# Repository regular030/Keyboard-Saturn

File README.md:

# **Keyboard Saturn, A Simple Keyboard With An OLED Display**

# **YouTube Video:**
https://youtu.be/Gn7tNZ5N1NY

# **Why Did I Make This**

After Hackpad, I started getting recommended lots of Scotto Keebs videos on YouTube, which made me much more interested in making my own keyboard. Now that I have more free time, I decided to make my 5-month-in-thought project a reality.

# **Design Choices**
- SN74HC165N
  - Instead of using any other GPIO expanders, I wanted to use the SN because it is an 8-bit parallel-load shift register, instead of using the I2C protocol to communicate with the MCU, which is around 8 times faster
- Raspberry Pi Pico
  - Cheap and Reliable
- OLED 32-128
  -  Just wanted to add a display where I can show whether or not NUM/CAPS/SCRL lock is on, + show Spotify music, + other stuff
- 100% Layout
  - I use the Numpad for anything numbers-related
- Minimalist chassis design
  - I just wanted to make something  that was simple and looked clean, kind of like Cybertruck, but better 
 
# **Files**
<br>
chassis
<br>

- .Step files for the chassis + PCB
  - KeyboardL.step
      - Bottom left side of keyboard
  - KeyboardM.step
      - Bottom middle side of keyboard
  - KeyboardR.step
      - Bottom right side of keyboard
  - KeyboardTop.step
      - Top side of the keyboard
      - Use M2 screws to screw it into the bottom parts (screw holes in top and bottom in the middle, left and right sections) 
  - insert-keyboard v1.step
      - The inserts for the keyboard to connect KeyboardM, KeyboardL and KeyboardR, please use super glue to make sure they are in, then super glue the chassis together
<br>
kicad
<br>

- All the KiCad 8.0.5 files for the project 

# **BOM:**

https://docs.google.com/spreadsheets/d/1oLEcZ3zztSK3hqa6-qvamrNF2S6u_cLABAHxks2xx3M/edit?usp=sharing

# THIS PROJECT IS NOW DEPRECATED. IT WILL NOT BE GETTING ANY MORE SUPPORT. V2 is a possibility

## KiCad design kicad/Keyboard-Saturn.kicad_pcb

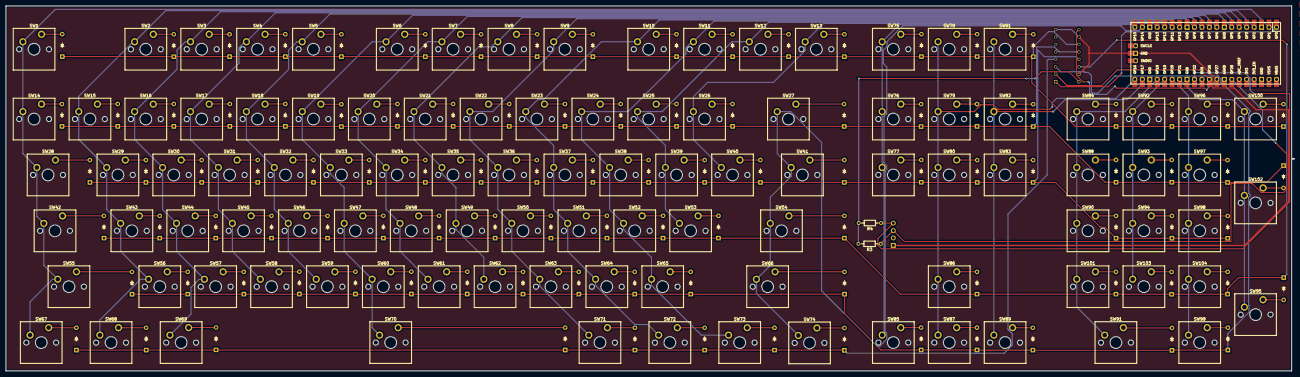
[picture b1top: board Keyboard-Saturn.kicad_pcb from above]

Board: 2 copper layers, 438.9 x 124.3 mm, 213 parts (1 on the bottom side), 138 nets.

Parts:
D1, D2, D3, D4, D5, D6, D7, D8, D9, D10, D11, D12, D13, D14, D15, D16, D17, D18, D19, D20, D21, D22, D23, D24, D25, D26, D27, D28, D29, D30, D31, D32, D33, D34, D35, D36, D37, D38, D39, D40, D41, D42, D43, D44, D45, D46, D47, D48, D49, D50, D51, D52, D53, D54, D55, D56, D57, D58, D59, D60, D61, D62, D63, D64, D65, D66, D67, D68, D69, D70, D71, D72, D73, D74, D75, D76, D77, D78, D79, D80, D81, D82, D83, D84, D85, D86, D87, D88, D89, D90, D91, D92, D93, D94, D95, D96, D97, D98, D99, D100, D101, D102, D103, D104: D; Diode_DO-35
J1: OLED_128x32
R3, R4: 2k; R_Axial_DIN0204_L3.6mm_D1.6mm_P7.62mm_Horizontal
SW1, SW2, SW3, SW4, SW5, SW6, SW7, SW8, SW9, SW10, SW11, SW12, SW13, SW14, SW15, SW16, SW17, SW18, SW19, SW20, SW21, SW22, SW23, SW24, SW25, SW26, SW29, SW30, SW31, SW32, SW33, SW34, SW35, SW36, SW37, SW38, SW39, SW40, SW43, SW44, SW45, SW46, SW47, SW48, SW49, SW50, SW51, SW52, SW53, SW56, SW57, SW58, SW59, SW60, SW61, SW62, SW63, SW64, SW65, SW75, SW76, SW77, SW78, SW79, SW80, SW81, SW82, SW83, SW84, SW85, SW86, SW87, SW88, SW89, SW90, SW92, SW93, SW94, SW96, SW97, SW98, SW99, SW100, SW101, SW103, SW104: SW_Push; MX_PCB_1.00u
SW27, SW91: SW_Push; MX_PCB_2.00u
SW28, SW41: SW_Push; MX_PCB_1.50u
SW42: SW_Push; MX_PCB_1.75u
SW54, SW55: SW_Push; MX_PCB_2.25u
SW66: SW_Push; MX_PCB_2.75u
SW67, SW68, SW69, SW71, SW72, SW73, SW74: SW_Push; MX_PCB_1.25u
SW70: SW_Push; MX_PCB_6.25u
SW95, SW102: SW_Push; MX_PCB_2.00u_90deg
U1: Raspberry_Pi_Pico
U3: SN74HC165N; DIP794W45P254L1969H508Q16

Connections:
+3.3V: R3.2, R4.2, U3.16 (VCC)
GND: J1.1 (GND), U1.42 (GND), U3.8 (GND), U3.10 (SER), U3.15 (CLK_INH)
unnamed: D1.2 (A), SW1.2
unnamed: D2.2 (A), SW2.2
unnamed: D3.2 (A), SW3.2
unnamed: D4.2 (A), SW4.2
unnamed: D5.2 (A), SW5.2
unnamed: D6.2 (A), SW6.2
unnamed: D7.2 (A), SW7.2
unnamed: D8.2 (A), SW8.2
unnamed: D9.2 (A), SW9.2
unnamed: D10.2 (A), SW10.2
unnamed: D11.2 (A), SW11.2
unnamed: D12.2 (A), SW12.2
unnamed: D13.2 (A), SW13.2
unnamed: D14.2 (A), SW14.2
unnamed: D15.2 (A), SW15.2
unnamed: D16.2 (A), SW16.2
unnamed: D17.2 (A), SW17.2
unnamed: D18.2 (A), SW18.2
unnamed: D19.2 (A), SW19.2
unnamed: D20.2 (A), SW20.2
unnamed: D21.2 (A), SW21.2
unnamed: D22.2 (A), SW22.2
unnamed: D23.2 (A), SW23.2
unnamed: D24.2 (A), SW24.2
unnamed: D25.2 (A), SW25.2
unnamed: D26.2 (A), SW26.2
unnamed: D27.2 (A), SW27.2
unnamed: D28.2 (A), SW28.2
unnamed: D29.2 (A), SW29.2
unnamed: D30.2 (A), SW30.2
unnamed: D31.2 (A), SW31.2
unnamed: D32.2 (A), SW32.2
unnamed: D33.2 (A), SW33.2
unnamed: D34.2 (A), SW34.2
unnamed: D35.2 (A), SW35.2
unnamed: D36.2 (A), SW36.2
unnamed: D37.2 (A), SW37.2
unnamed: D38.2 (A), SW38.2
unnamed: D39.2 (A), SW39.2
unnamed: D40.2 (A), SW40.2
unnamed: D41.2 (A), SW41.2
unnamed: D42.2 (A), SW42.2
unnamed: D43.2 (A), SW43.2
unnamed: D44.2 (A), SW44.2
unnamed: D45.2 (A), SW45.2
unnamed: D46.2 (A), SW46.2
unnamed: D47.2 (A), SW47.2
unnamed: D48.2 (A), SW48.2
unnamed: D49.2 (A), SW49.2
unnamed: D50.2 (A), SW50.2
unnamed: D51.2 (A), SW51.2
unnamed: D52.2 (A), SW52.2
unnamed: D53.2 (A), SW53.2
unnamed: D54.2 (A), SW54.2
unnamed: D55.2 (A), SW55.2
unnamed: D56.2 (A), SW56.2
unnamed: D57.2 (A), SW57.2
unnamed: D58.2 (A), SW58.2
unnamed: D59.2 (A), SW59.2
unnamed: D60.2 (A), SW60.2
unnamed: D61.2 (A), SW61.2
unnamed: D62.2 (A), SW62.2
unnamed: D63.2 (A), SW63.2
unnamed: D64.2 (A), SW64.2
unnamed: D65.2 (A), SW65.2
unnamed: D66.2 (A), SW66.2
unnamed: D67.2 (A), SW67.2
unnamed: D68.2 (A), SW68.2
unnamed: D69.2 (A), SW69.2
unnamed: D70.2 (A), SW70.2
unnamed: D71.2 (A), SW71.2
unnamed: D72.2 (A), SW72.2
unnamed: D73.2 (A), SW73.2
unnamed: D74.2 (A), SW74.2
unnamed: D75.2 (A), SW75.2
unnamed: D76.2 (A), SW76.2
unnamed: D77.2 (A), SW77.2
unnamed: D78.2 (A), SW78.2
unnamed: D79.2 (A), SW79.2
unnamed: D80.2 (A), SW80.2
unnamed: D81.2 (A), SW81.2
unnamed: D82.2 (A), SW82.2
unnamed: D83.2 (A), SW83.2
unnamed: D84.2 (A), SW84.2
unnamed: D85.2 (A), SW85.2
unnamed: D86.2 (A), SW86.2
unnamed: D87.2 (A), SW87.2
unnamed: D88.2 (A), SW88.2
unnamed: D89.2 (A), SW89.2
unnamed: D90.2 (A), SW90.2
unnamed: D91.2 (A), SW91.2
unnamed: D92.2 (A), SW92.2
unnamed: D93.2 (A), SW93.2
unnamed: D94.2 (A), SW94.2
unnamed: D95.2 (A), SW95.2
unnamed: D96.2 (A), SW96.2
unnamed: D97.2 (A), SW97.2
unnamed: D98.2 (A), SW98.2
unnamed: D99.2 (A), SW99.2
unnamed: D100.2 (A), SW100.2
unnamed: D101.2 (A), SW101.2
unnamed: D102.2 (A), SW102.2
unnamed: D103.2 (A), SW103.2
unnamed: D104.2 (A), SW104.2
unnamed: U1.1 (GPIO0), U3.1 (SH/~LD)
unnamed: U1.31 (GPIO26_ADC0), U3.2 (CLK)
unnamed: U1.32 (GPIO27_ADC1), U3.9 (QH)
SCL: J1.3 (SCL), R3.1, U1.34 (GPIO28_ADC2)
SDA: J1.4 (SDA), R4.1, U1.29 (GPIO22)
col 1: SW1.1, SW14.1, SW28.1, SW42.1, SW55.1, SW67.1, U1.2 (GPIO1)
col 2: SW2.1, SW15.1, SW29.1, SW43.1, SW56.1, SW68.1, U1.4 (GPIO2)
col 3: SW3.1, SW16.1, SW30.1, SW44.1, SW57.1, SW69.1, U1.5 (GPIO3)
col 4: SW4.1, SW17.1, SW31.1, SW45.1, SW58.1, U1.6 (GPIO4)
col 5: SW5.1, SW18.1, SW32.1, SW46.1, SW59.1, U1.7 (GPIO5)
col 6: SW6.1, SW19.1, SW33.1, SW47.1, SW60.1, SW70.1, U1.9 (GPIO6)
col 7: SW7.1, SW20.1, SW34.1, SW48.1, SW61.1, U1.10 (GPIO7)
col 8: SW8.1, SW21.1, SW35.1, SW49.1, SW62.1, U1.11 (GPIO8)
col 9: SW9.1, SW22.1, SW36.1, SW50.1, SW63.1, SW71.1, U1.12 (GPIO9)
col 10: SW10.1, SW23.1, SW37.1, SW51.1, SW64.1, SW72.1, U1.14 (GPIO10)
col 11: SW11.1, SW24.1, SW38.1, SW52.1, SW65.1, SW73.1, U1.15 (GPIO11)
col 12: SW12.1, SW25.1, SW39.1, SW53.1, U1.16 (GPIO12)
col 13: SW13.1, SW26.1, SW40.1, U1.17 (GPIO13)
col 14: SW27.1, SW41.1, SW54.1, SW66.1, SW74.1, U1.19 (GPIO14)
col 15: SW75.1, SW76.1, SW77.1, SW85.1, U1.20 (GPIO15)
col 16: SW78.1, SW79.1, SW80.1, SW86.1, SW87.1, U1.21 (GPIO16)
col 17: SW81.1, SW82.1, SW83.1, SW89.1, U1.22 (GPIO17)
col 18: SW84.1, SW88.1, SW90.1, SW91.1, SW101.1, U1.24 (GPIO18)
col 19: SW92.1, SW93.1, SW94.1, SW103.1, U1.25 (GPIO19)
col 20: SW96.1, SW97.1, SW98.1, SW99.1, SW104.1, U1.26 (GPIO20)
col 21: SW95.1, SW100.1, SW102.1, U1.27 (GPIO21)
row 1: D1.1 (K), D2.1 (K), D3.1 (K), D4.1 (K), D5.1 (K), D6.1 (K), D7.1 (K), D8.1 (K), D9.1 (K), D10.1 (K), D11.1 (K), D12.1 (K), D13.1 (K), D75.1 (K), D78.1 (K), D81.1 (K), D84.1 (K), D92.1 (K), D96.1 (K), D100.1 (K), U3.11 (A)
row 2: D14.1 (K), D15.1 (K), D16.1 (K), D17.1 (K), D18.1 (K), D19.1 (K), D20.1 (K), D21.1 (K), D22.1 (K), D23.1 (K), D24.1 (K), D25.1 (K), D26.1 (K), D27.1 (K), D76.1 (K), D79.1 (K), D82.1 (K), D88.1 (K), D93.1 (K), D97.1 (K), D102.1 (K), U3.12 (B)
row 3: D28.1 (K), D29.1 (K), D30.1 (K), D31.1 (K), D32.1 (K), D33.1 (K), D34.1 (K), D35.1 (K), D36.1 (K), D37.1 (K), D38.1 (K), D39.1 (K), D40.1 (K), D41.1 (K), D77.1 (K), D80.1 (K), D83.1 (K), D90.1 (K), D94.1 (K), D98.1 (K), U3.13 (C)
row 4: D42.1 (K), D43.1 (K), D44.1 (K), D45.1 (K), D46.1 (K), D47.1 (K), D48.1 (K), D49.1 (K), D50.1 (K), D51.1 (K), D52.1 (K), D53.1 (K), D54.1 (K), D86.1 (K), D95.1 (K), D101.1 (K), D103.1 (K), D104.1 (K), U3.14 (D)
row 5: D55.1 (K), D56.1 (K), D57.1 (K), D58.1 (K), D59.1 (K), D60.1 (K), D61.1 (K), D62.1 (K), D63.1 (K), D64.1 (K), D65.1 (K), D66.1 (K), D85.1 (K), D87.1 (K), D89.1 (K), D91.1 (K), D99.1 (K), U3.3 (E)
row 6: D67.1 (K), D68.1 (K), D69.1 (K), D70.1 (K), D71.1 (K), D72.1 (K), D73.1 (K), D74.1 (K), U3.4 (F)

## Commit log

2025-05-20 Updated names
2025-05-20 updated some documentation
2025-05-21 chassis v1
2025-05-21 chassis final???
2025-05-23 made my chassis printable on a a1m
2025-05-23 file reorg
2025-05-24 added SN34HC165N to kicad
2025-05-24 generate gerber, update PCB step + finshed PCB wiring
2025-05-24 update 3d model, and added copper fills
2025-05-25 90% done firmware, updated kicad files to match code
2025-05-28 added palm rest on keyboard
2025-05-29 realized there was a hole missing on keyboardBotL and R
2025-07-11 moved code to arudino ide, keyboard works, more stuff coming soon
2025-07-18 kill me. Added OLED support.
2025-07-18 Update JOURNAL.md - Pics to be added
